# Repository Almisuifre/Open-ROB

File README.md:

# Open-ROB
Un robot modulaire open source.

L'ensemble repose sur des logiciels Open Source

LICENCE

<br /><span xmlns:dct="http://purl.org/dc/terms/" property="dct:title">Open-ROB</span> de <a xmlns:cc="http://creativecommons.org/ns#" href="https://github.com/Almisuifre/Open-ROB" property="cc:attributionName" rel="cc:attributionURL">Almisuifre</a> est mis à disposition selon les termes de la <a rel="license" href="http://creativecommons.org/licenses/by-sa/4.0/">licence Creative Commons Attribution -  Partage dans les Mêmes Conditions 4.0 International</a>.

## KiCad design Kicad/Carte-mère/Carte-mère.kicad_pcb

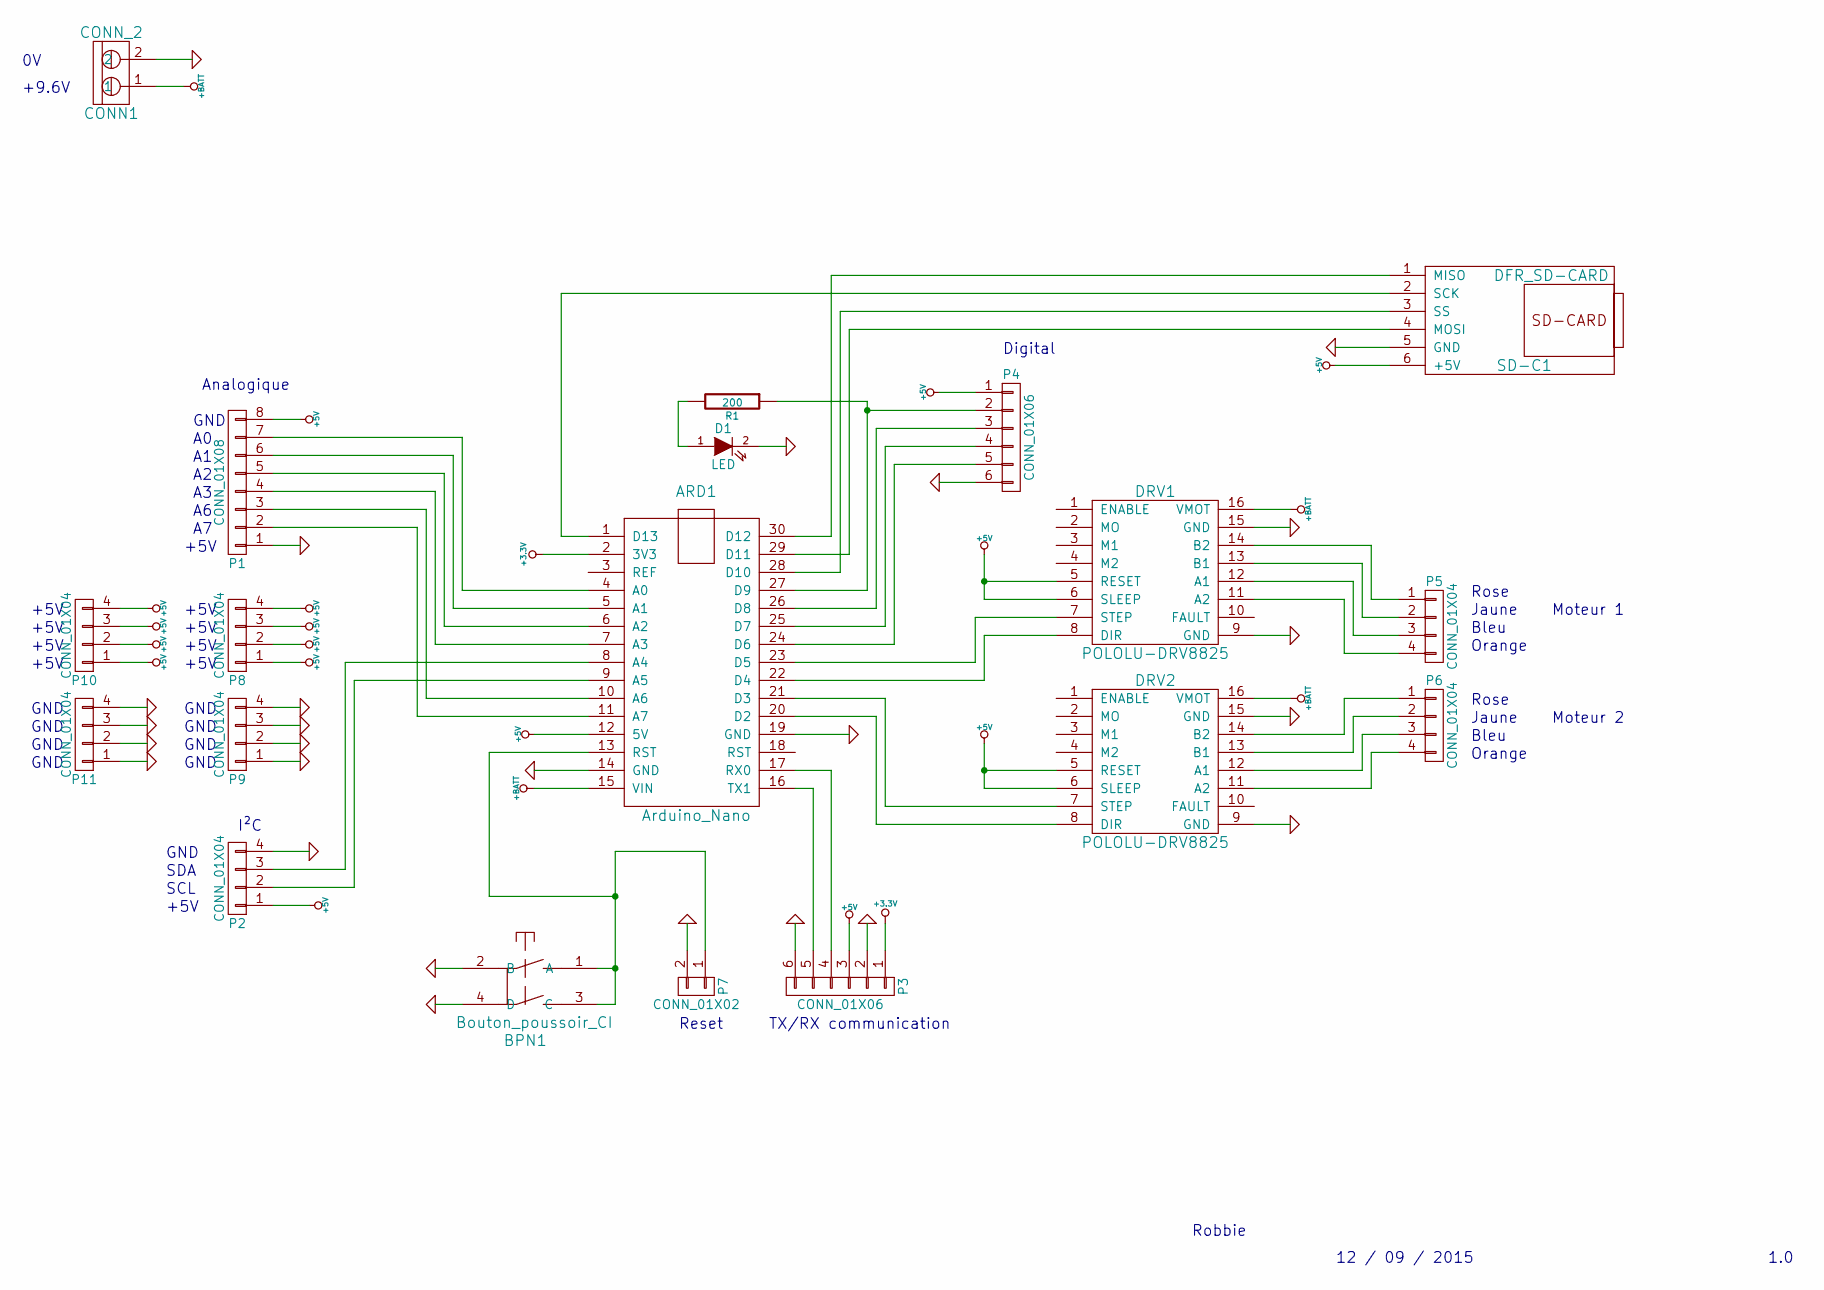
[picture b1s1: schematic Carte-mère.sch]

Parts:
ARD1: Arduino_Nano; Arduino Nano
BPN1: Bouton_poussoir_CI; BPN-CI
CONN1: CONN_2; bornier2
D1: LED; LED-0603
DRV1, DRV2: POLOLU-DRV8825
P1: CONN_01X08; Pin_Header_Straight_1x08
P2, P5, P6, P8, P9, P10, P11: CONN_01X04; Pin_Header_Straight_1x04
P3, P4: CONN_01X06; Pin_Header_Straight_1x06
P7: CONN_01X02; Pin_Header_Straight_1x02
R1: 200; R_0603_HandSoldering
SD-C1: DFR_SD-CARD

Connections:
+3.3V: ARD1.2 (3V3), P3.1
+5V: ARD1.12 (5V), DRV1.5 (RESET), DRV1.6 (SLEEP), DRV2.5 (RESET), DRV2.6 (SLEEP), P1.8, P2.1, P3.3, P4.1, P8.1, P8.2, P8.3, P8.4, P10.1, P10.2, P10.3, P10.4, SD-C1.6 (+5V)
+BATT: ARD1.15 (VIN), CONN1.1, DRV1.16 (VMOT), DRV2.16 (VMOT)
GND: ARD1.14 (GND), ARD1.19 (GND), BPN1.2 (B), BPN1.4 (D), CONN1.2, D1.2 (K), DRV1.9 (GND), DRV1.15 (GND), DRV2.9 (GND), DRV2.15 (GND), P1.1, P2.4, P3.2, P3.6, P4.6, P7.2, P9.1, P9.2, P9.3, P9.4, P11.1, P11.2, P11.3, P11.4, SD-C1.5 (GND)
unnamed: ARD1.1 (D13), SD-C1.2 (SCK)
unnamed: ARD1.4 (A0), P1.7
unnamed: ARD1.5 (A1), P1.6
unnamed: ARD1.6 (A2), P1.5
unnamed: ARD1.7 (A3), P1.4
unnamed: ARD1.8 (A4), P2.3
unnamed: ARD1.9 (A5), P2.2
unnamed: ARD1.10 (A6), P1.3
unnamed: ARD1.11 (A7), P1.2
unnamed: ARD1.13 (RST), BPN1.1 (A), BPN1.3 (C), P7.1
unnamed: ARD1.16 (TX1), P3.5
unnamed: ARD1.17 (RX0), P3.4
unnamed: ARD1.20 (D2), DRV2.8 (DIR)
unnamed: ARD1.21 (D3), DRV2.7 (STEP)
unnamed: ARD1.22 (D4), DRV1.8 (DIR)
unnamed: ARD1.23 (D5), DRV1.7 (STEP)
unnamed: ARD1.24 (D6), P4.5
unnamed: ARD1.25 (D7), P4.4
unnamed: ARD1.26 (D8), P4.3
unnamed: ARD1.27 (D9), P4.2, R1.1
unnamed: ARD1.28 (D10), SD-C1.3 (SS)
unnamed: ARD1.29 (D11), SD-C1.4 (MOSI)
unnamed: ARD1.30 (D12), SD-C1.1 (MISO)
unnamed: D1.1 (A), R1.2
unnamed: DRV1.11 (A2), P5.4
unnamed: DRV1.12 (A1), P5.3
unnamed: DRV1.13 (B1), P5.2
unnamed: DRV1.14 (B2), P5.1
unnamed: DRV2.11 (A2), P6.4
unnamed: DRV2.12 (A1), P6.3
unnamed: DRV2.13 (B1), P6.2
unnamed: DRV2.14 (B2), P6.1

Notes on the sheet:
Moteur 1
Moteur 2
Rose
Jaune
Bleu
Orange
+9.6V
I²C
GND
SCL
SDA
+5V
Analogique
Digital
Robbie
12 / 09 / 2015
1.0
TX/RX communication
Reset

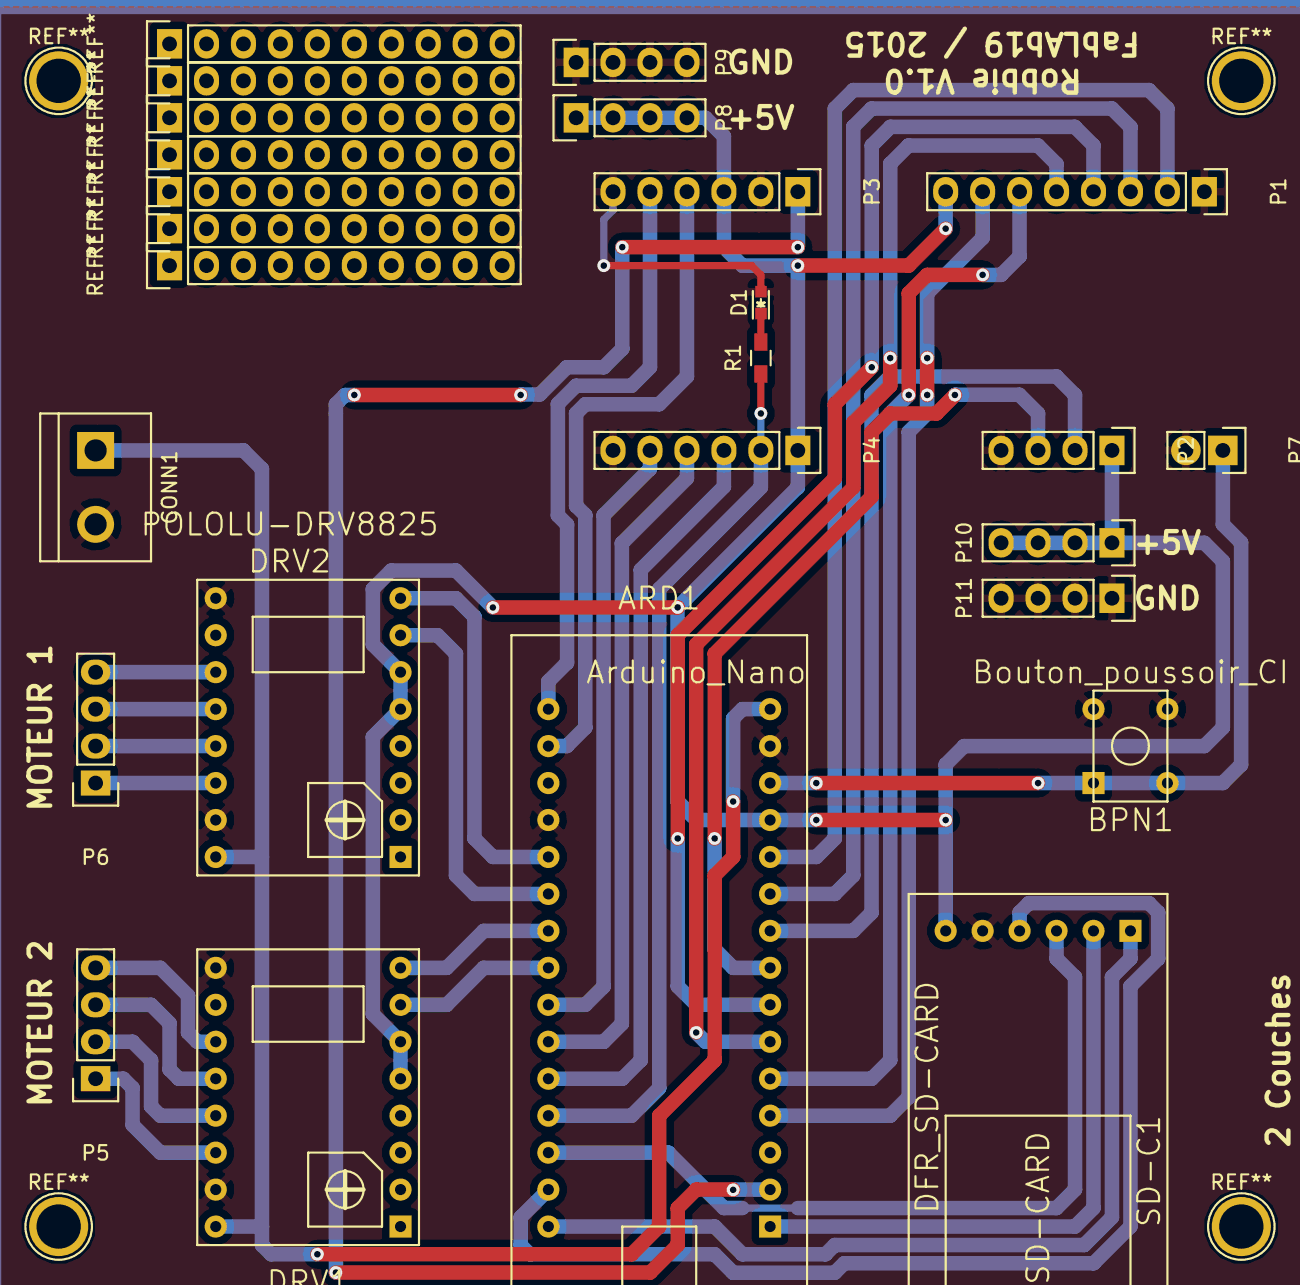
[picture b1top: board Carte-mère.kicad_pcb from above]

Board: 2 copper layers, 19 parts (0 on the bottom side), 36 nets.

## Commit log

2015-08-19 Création du répertoire FreeCAD
2015-08-19 Mise à jour de la licence
2015-08-20 Ajout du stepper
2015-08-20 Ajout de la batterie
2015-08-20 Erreur d'exportation de la batterie
2015-08-20 Rectification de l'erreur d'exportation
2015-08-22 Ajout du train planétaire
2015-08-22 Ajout de la visserie M3
2015-08-22 Ajout rondelle M3
2015-08-24 Retraît du train planétaire jugé trop complexe
2015-08-26 Modification du stepper
2015-08-26 Ajout d'un axe Moteur-Roue prise directe
2015-08-26 Ajout d'un assemblage
2015-08-27 Création du couvercle qui retient l'axe qui fait interface entre la roue et le moteur pas à pas
2015-08-27 Modification de l'assemblage
2015-08-27 Mise à jour du couvercle
2015-08-27 Création des roues
2015-08-27 Mise à jour de l'assemblage
2015-08-27 Ajout d'une chaussette pour améliorer le contact avec le sol
2015-08-27 Révision de l'assemblage
2015-08-28 Création d'une equerre de fixation pour le moteur pas à pas
2015-08-28 Mise à jour de l'assemblage pour inclure l'équerre
2015-08-28 Modification de l'axe Moteur - Roue
2015-08-28 Ajout de la roue folle
2015-08-29 Ajout d'une partie pour garantir le paintient du stepper en place
2015-08-30 Ajout d'une roue au version 2
2015-08-30 Création d'un plateau
2015-08-30 Modification du plateau
2015-09-01 Retrait du plateau
2015-09-03 Ajout d'un corner pour la nacelle
2015-09-03 Ajout d'un corner pour faire la nacelle
2015-09-03 Refonte complète de l'assemblage
2015-09-03 Modification des bras
2015-09-05 Modification du bras
2015-09-05 Modification du corner de la nacelle
2015-09-08 Ajout d'un bras vers la roue folle
2015-09-08 Ajout d'un support de batterie à la nacelle
2015-09-11 Ajout du roulement à bille
2015-09-11 Ajout d'une roue folle attapté au châssis
2015-09-12 Ajout de la construction d'un PCB
2015-09-13 Modification du circuit imprimée
2015-09-13 Mise à jour de la carte mère
2015-09-14 Modification PCB pour prendre en compte les remarques faites à l'IUT
2015-09-19 Mise en place des capteurs GPD2
2015-09-19 Ajout des capteurs SHARP GPD2
2015-09-19 Ajout d'une liste de datasheet
2015-09-19 Ajout de la refonte de la carte mère
2015-09-20 Retrait des capteurs GPD2
2015-09-24 Mise en place des capteurs sur le châssis
2015-09-24 Modif readme, ajout de "modulaire"
2015-09-24 Ajout gitignore pour ignorer les fichier de backup (fcstd1)
2015-09-24 Placement et retouche
    Ajustement de la longueur de Support Batterie A
    Placement des pièce du cadre pour éviter les chevauchements
2015-09-25 Ajout des vis dans l'assemblage
    Ajout des modèle de vis de différente longueure
    Suppression des backup (ajout des fcstd1 à gitignore)
2015-09-25 Mise à jour du PCB
2015-12-22 Rectification d'une annotation incorrect sur P1. Non impacté sur le PCB
2015-12-23 Ajout de la carte mère
2015-12-23 Ajout du suport de carte mère et fixation sur la nacelle
2015-12-23 Ajout des modiffications sur l'assemblage
2015-12-24 Ajout du début de programme embarqué de Robbie
2015-12-25 Retraît du répertoire contenu dans Arduino suite à une erreur de saisie
2015-12-25 Ajout du répertoire Programmations/Arduino/Robbie-V1.0
2015-12-25 Ajout classe sonar et tests
2015-12-25 Ajout d'un sonar MaxSonar MB1010
2015-12-26 Ajout d'une interface Sonar
2015-12-26 Ajout d'une série de visserie M3x12
2015-12-26 Mise à jour assemblage
2015-12-27 Mise à jour du programme de test
